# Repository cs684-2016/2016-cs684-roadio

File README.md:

# 2016-cs684-roadio
Road i/o: Road quality measurement, monitoring and mapping solution [Course project for CS684: Embedded Systems]

Link to git repo: https://github.com/shalaka-kulkarni/2016-cs684-roadio

Link to the screencast video for building the CCS project: https://drive.google.com/file/d/0ByCbdaDy1kjwQkpVakRZU1czRE0/view?usp=sharing

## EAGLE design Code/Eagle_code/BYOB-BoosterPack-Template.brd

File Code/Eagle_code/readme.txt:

Eagle files for GPS Module and BoosterPack Module
BoostePack has GPS Module, Ultrasonic Sesnor, Accelerometer, SD Card & Voltage Regulator.

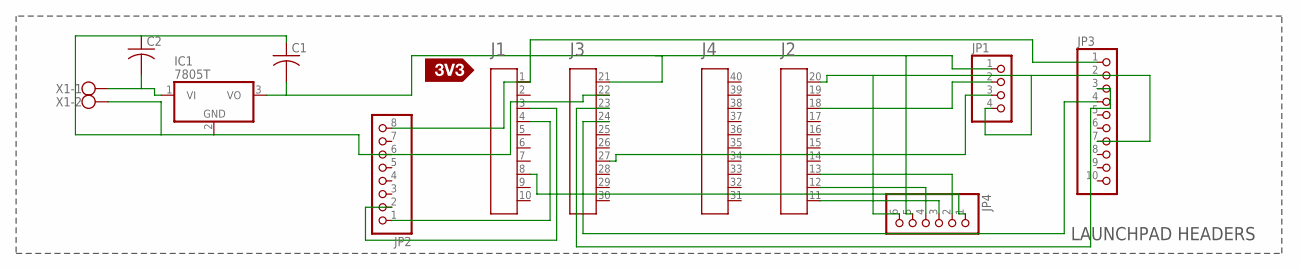
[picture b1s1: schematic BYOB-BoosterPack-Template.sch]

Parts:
A1: HEADER4X10-BOOSTERPACK; 4X10-BOOSTERPACK
C1, C2: C-US025-025X050; C025-025X050
IC1: 7805T; TO220H
JP1: PINHD-1X4; 1X04
JP2: PINHD-1X8; 1X08
JP3: PINHD-1X10; 1X10
JP4: PINHD-1X6; 1X06
U$3: SILK_3V3_TAG
X1: W237-102

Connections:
GND: A1.20, A1.22, C1.1, C2.1, IC1.2 (GND), JP1.4, JP2.6, JP3.2, JP3.7, JP4.6, X1.2
unnamed: A1.21, C1.2, IC1.3 (VO), JP1.1, JP4.5
unnamed: A1.4, JP2.1
unnamed: A1.18, JP1.2
unnamed: A1.27, JP1.3
unnamed: A1.1, JP2.8, JP3.1
unnamed: A1.3, JP2.2
unnamed: A1.24, JP3.4
unnamed: A1.23, JP3.3
unnamed: A1.12, JP4.4
unnamed: A1.11, JP4.3
unnamed: A1.13, JP4.2
unnamed: A1.8, JP4.1
unnamed: C2.2, IC1.1 (VI), X1.1

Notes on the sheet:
LAUNCHPAD HEADERS

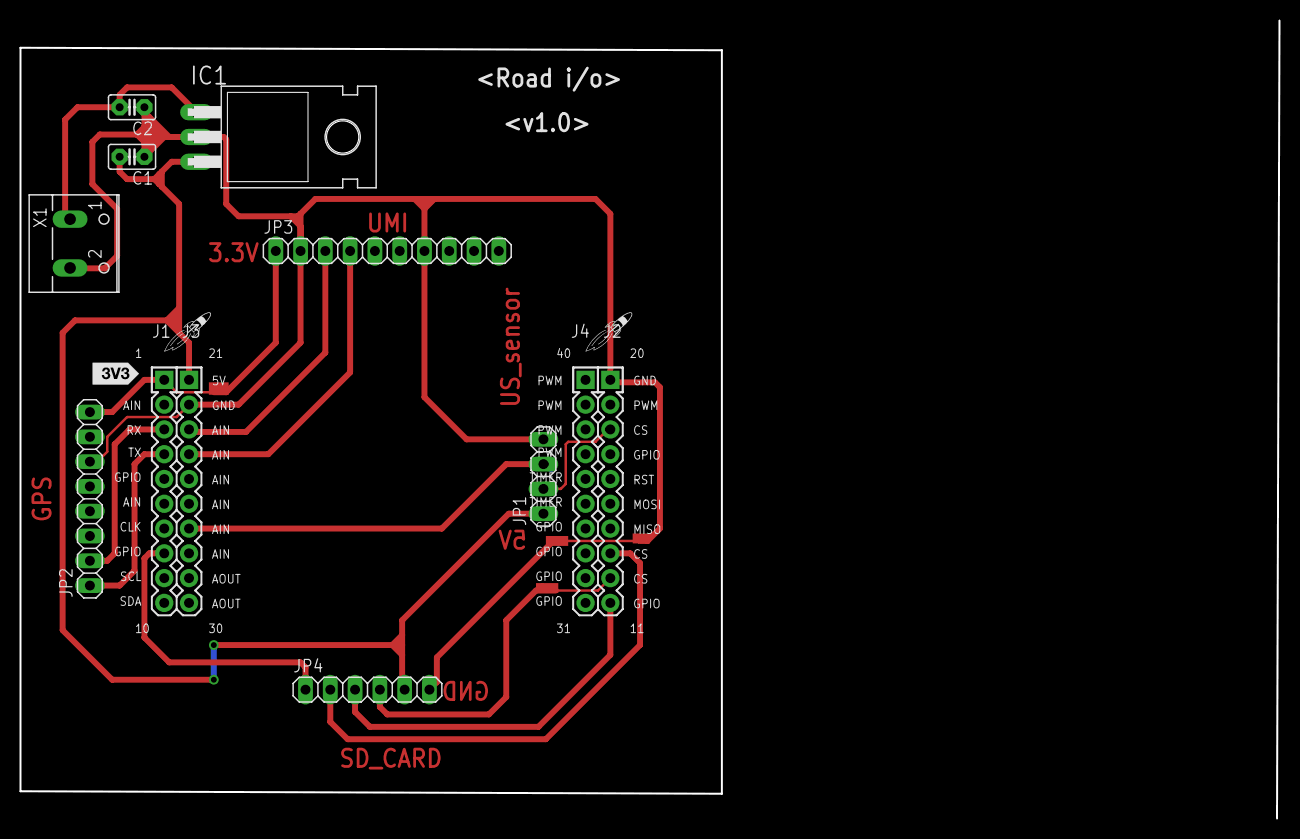
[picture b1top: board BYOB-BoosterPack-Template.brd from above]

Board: 2 copper layers, 71.9 x 76.5 mm, 12 parts (0 on the bottom side), 14 nets.

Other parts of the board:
U$1, U$2: LOGO-ROCKET

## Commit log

2016-10-26 Final documented code
2016-10-26 Create UI_Code
2016-10-26 Documented code
2016-11-04 Add the link to screencast video
2016-11-05 Remove the current report
2016-11-05 Add the new report
2016-11-05 Add the CCS project
